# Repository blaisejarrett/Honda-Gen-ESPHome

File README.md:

# Honda-Gen-ESPHome
Honda EU7000is Generator [ESPHome](https://esphome.io/) Integration.

It enables Remote Start and extensive sensor monitoring on the
Fuel Injected Honda EU7000is over wifi.

This project provides two Integrations. They can be used separately or together.

Addionally there is Open Source hardware available for use or for reference
[Here](hardware/README.md)

## Remote Start

Provides a Home Assistant Switch which implements remote start logic.

You must provide 3 GPIO inputs for this to work:
* (Input) Engine running
* (Output) Start Button
* (Output) Engine Kill Switch

In addition, you can optionally provide
* (Input) Power Switch Sensor

If you provide the power switch sensor it will not allow start attempts
if the engine power switch is off.

**Example GPIO configurations**:
```yaml
binary_sensor:
  - platform: gpio
    pin: ${run_pin}
    name: "${upper_devicename} Running Light"
    id: "run_sensor"
  - platform: gpio
    pin: ${sw_pin}
    name: "${upper_devicename} Power Sw Enabled"
    id: "power_sw_sensor"

output:
  - platform: gpio
    pin: ${start_pin}
    id: "start_button"
  - platform: gpio
    pin: ${stop_pin}
    id: "stop_relay"
```

**Example Remote Start Switch Configuration**

```yaml
switch:
  - platform: honda_gen_remote_start
    name: "${upper_devicename} Remote Start"
    # This one's optional. If you provide it then it won't
    # allow start attempts if the power switch is off.
    power_sw_input: power_sw_sensor
    # The following are required.
    run_input: run_sensor
    start_output: start_button
    stop_output: stop_relay
```

For a full example see [Here](example_honda_gen_remote_start.yaml)

## Data Link Connector (DLC) Sensors
The EU7000is is Fuel Injected and features an engine computer.
You can read the ECU's sensor values via a UART bus.

This integration implements a UART device which provides a number of sensors.

Some of the more useful ones:
* Power Output
    * Combined and for each phase
* Engine RPM
* Eco mode on/off
* Engine Throttle
* Engine Run Time
* Temperatures

To use this you must provide a UART interface. There are some hardware considerations.
I recommend you check out the hardware portion of this project [here](hardware/README.md) for reference.

**Implement a UART interface:**
```yaml
uart:
  rx_pin: ${dlc_rx_pin}
  tx_pin: ${dlc_tx_pin}
  baud_rate: 9600
```
**Example Configuration**
```yaml
honda_gen_dlc:
  # if the power is off it won't bother attempting to query sensor values.
  power_switch: power_sw_sensor

  battery_voltage:
    name: "${upper_devicename} Battery Voltage"
  engine_rpm:
    name: "${upper_devicename} Engine RPM"
  runtime:
    name: "${upper_devicename} Total Engine Runtime"
  cylinder_head_temperature:
    name: "${upper_devicename} Cylinder Head Temperature"
  engine_timing:
    name: "${upper_devicename} Engine Spark Timing"
  output_voltage:
    name: "${upper_devicename} Output Voltage"

  barometric_pressure:
    name: "${upper_devicename} Barometric Pressure"
  fuel_injection_time:
    name: "${upper_devicename} Fuel Injection Time"
  throttle:
    name: "${upper_devicename} Trottle Position"
  output_power:
    name: "${upper_devicename} Output Power"
  starter_count:
    name: "${upper_devicename} Starter Count"
  o2_sensor:
    name: "${upper_devicename} O2 Sensor"

  inv_master_current:
    name: "${upper_devicename} Master Inv Current"
  inv_master_temperature:
    name: "${upper_devicename} Master Inv Temperature"
  inv_master_eco:
    name: "${upper_devicename} Eco Mode"
  inv_master_power:
    name: "${upper_devicename} Master Inv Power"
  inv_master_volts:
    name: "${upper_devicename} Master Inv Voltage"

  inv_slave_current:
    name: "${upper_devicename} Slave Inv Current"
  inv_slave_temperature:
    name: "${upper_devicename} Slave Inv Temperature"
  inv_slave_power:
    name: "${upper_devicename} Slave Inv Power"
```

You can optionally provide a power switch sensor. If you do it will not
attempt to query the ECU values over UART if the power switch is off.
Otherwise, it will continually send TX packets and time out if you do not
provide one and the Generator's power switch is off.

You can exclude any sensors from the configuration you do not find 
valuable. The complete list is in the configuration example above.

For a full example see [Here](example_honda_gen_dlc.yaml). Here's an example 
which [includes both integrations](example_honda_gen_complete.yaml).

## Installation with ESPHome

You can use install these integrations just by adding the following to your
esphome project's yaml.
```yaml
external_components:
  - source: github://blaisejarrett/Honda-Gen-ESPHome@main
    components: [ honda_gen_dlc, honda_gen_remote_start ]
```

## Disclaimer
This was tested on a Canadian Model EU7000is. I believe it will work
on US model's aswell. However, 2021+ US models have Bluetooth remote start
features built in. I am told that the remote start port functiality of
this model is different.

Hopefully it works for you. If it does or doesn't I would be interested in
updating this readme.

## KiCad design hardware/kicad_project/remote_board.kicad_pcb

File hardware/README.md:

# Honda Gen Remote Hardware

Here you will find a kicad project and schematic for building an esp32
remote for your honda EU7000is.

The purpose of this device is to interface an esp32 with the DLC port and
the remote start port. This project uses optical isolators between the 
generator and the esp32 microcontroller.

## Schematic
The schematic for this project is available [here](schematic.pdf?raw=true).

It's useful to reference the Honda Gen schematic aswell to understand how to wire
the connectors:

## The Remote Start Connector
The remote start connector uses a [Sumitomo HM 6090-1021 Connector](https://prd.sws.co.jp/components/en/detail.php?number_s=60901021)

It has 8 pins. 5 of which are populated.

| Pin | Description        | Color |
| --- | ------------------ | ----- |
| 1   | Kill SW p2         | Brown/Blue |
| 2   | Running Indicator  | Green/Blue |
| 3   | N/A                |       |
| 4   | N/A                |       |
| 5   | Kill SW p1         | White/Blue |
| 6   | Start              | White/Green |
| 7   | N/A                |       |
| 8   | GND                | Green |

When looking at the female connector on the generator. The pins
are in the following order:
```
8 7 6 5
4 3 2 1
```

## The DLC Connector
The physical connector is described here: https://github.com/blaisejarrett/Honda-Gen-PGM-FI-Protocol#physical-layer

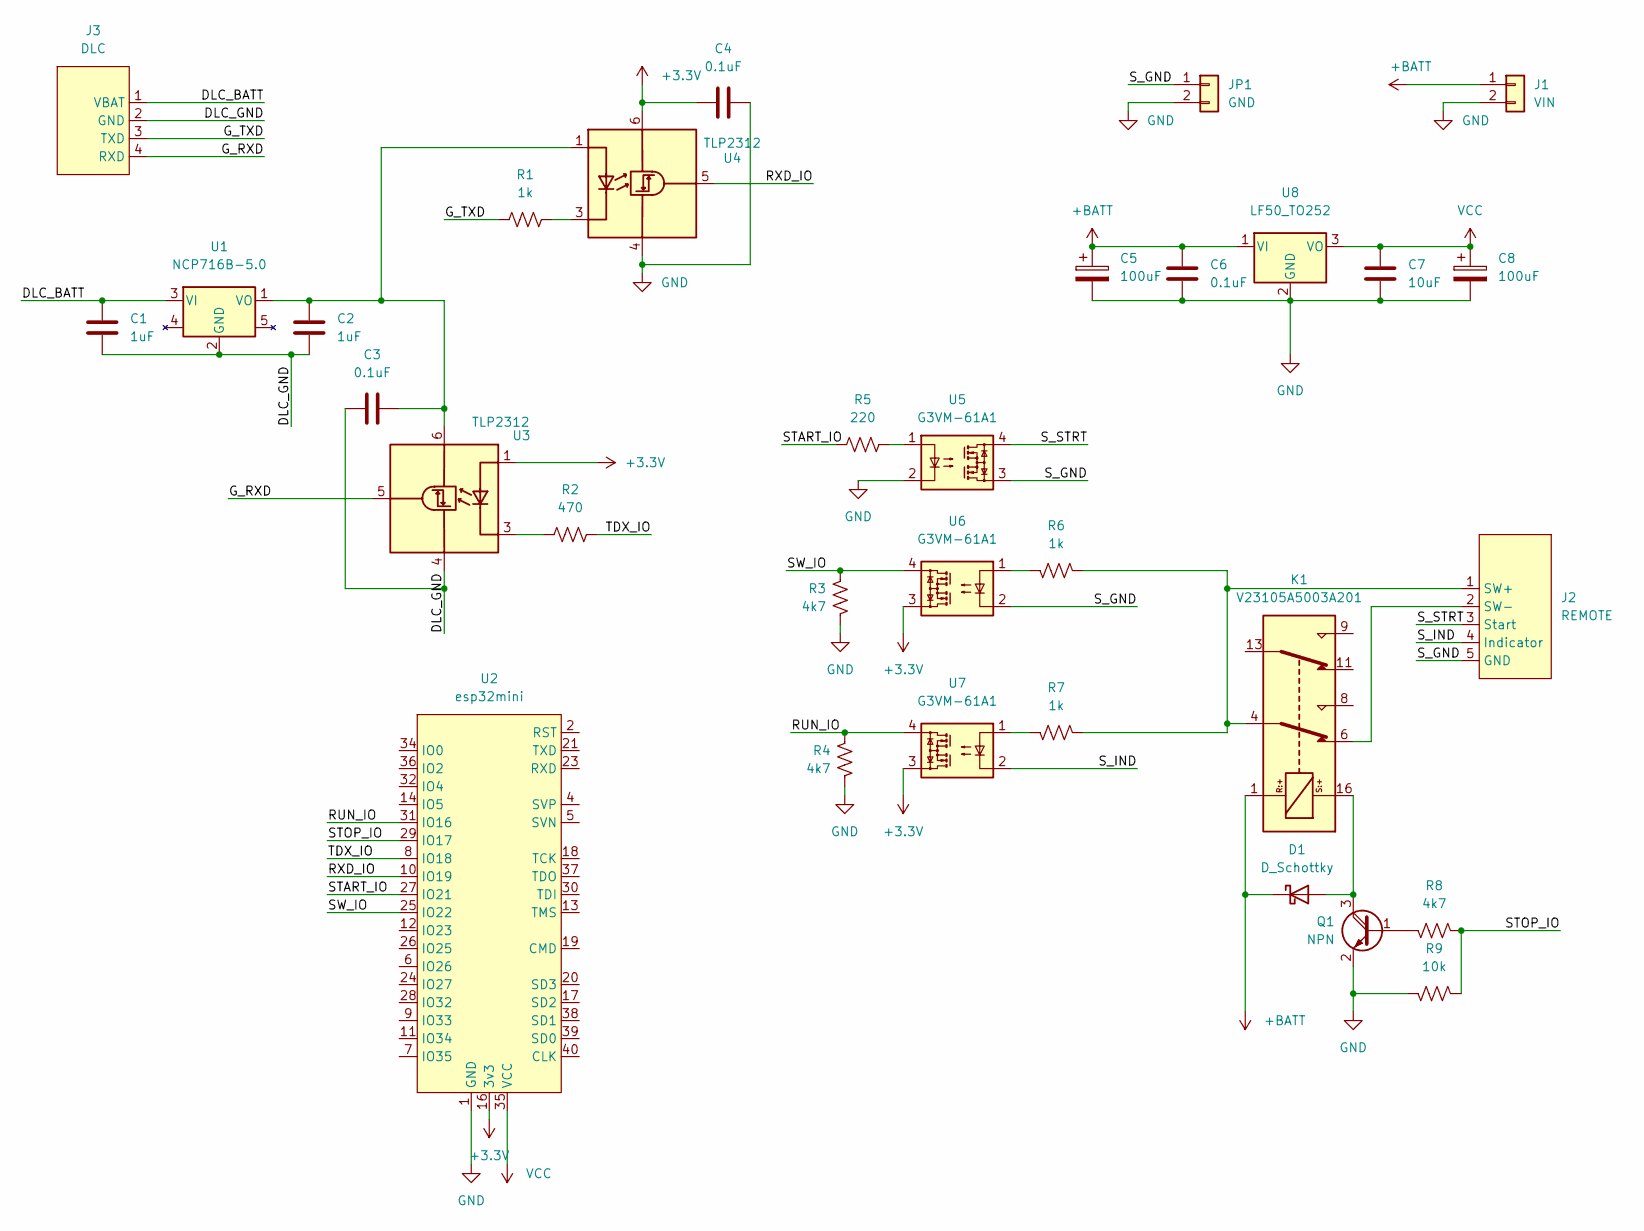
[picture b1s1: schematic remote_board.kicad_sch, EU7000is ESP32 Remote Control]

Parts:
C1, C2: 1uF; C_0805_2012Metric
C3, C4, C6: 0.1uF; C_0805_2012Metric
C5, C8: 100uF; CP_Elec_6.3x5.8
C7: 10uF; C_1206_3216Metric
D1: D_Schottky; D_0805_2012Metric
J1: VIN; PinHeader_1x02_P2.54mm_Vertical
J2: REMOTE; PinHeader_1x05_P2.54mm_Vertical
J3: DLC; PinHeader_1x04_P2.54mm_Vertical
JP1: GND; PinHeader_1x02_P2.54mm_Vertical
K1: V23105A5003A201
Q1: NPN; SOT-23
R1, R6, R7: 1k; R_0805_2012Metric
R2: 470; R_0805_2012Metric
R3, R4, R8: 4k7; R_0805_2012Metric
R5: 220; R_0805_2012Metric
R9: 10k; R_0805_2012Metric
U1: NCP716B-5.0; TSOP-5_1.65x3.05mm_P0.95mm
U2: esp32mini; ESP32_mini
U3, U4: TLP2312; SO-5_4.4x3.6mm_P1.27mm
U5, U6, U7: G3VM-61A1; DIP-4_W7.62mm
U8: LF50_TO252; TO-252-2

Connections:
+3V3: C4.1, U2.16 (3v3), U3.1 (A), U4.6 (VDD), U6.3, U7.3
+BATT: C5.1, C6.1, D1.1 (K), J1.1, K1.1, U8.1 (VI)
/DLC_BATT: C1.1, J3.1 (VBAT), U1.3 (VI)
/DLC_GND: C1.2, C2.2, C3.2, J3.2 (GND), U1.2 (GND), U3.4 (GND)
/G_RXD: J3.4 (RXD), U3.5 (VO)
/G_TXD: J3.3 (TXD), R1.1
/RUN_IO: R4.2, U2.31 (IO16), U7.4
/RXD_IO: U2.10 (IO19), U4.5 (VO)
/START_IO: R5.1, U2.27 (IO21)
/STOP_IO: R8.1, R9.1, U2.29 (IO17)
/SW_IO: R3.2, U2.25 (IO22), U6.4
/S_GND: J2.5 (GND), JP1.1, U5.3, U6.2
/S_IND: J2.4 (Indicator), U7.2
/S_STRT: J2.3 (Start), U5.4
/TDX_IO: R2.2, U2.8 (IO18)
GND: C4.2, C5.2, C6.2, C7.2, C8.2, J1.2, JP1.2, Q1.2 (E), R3.1, R4.1, R9.2, U2.1 (GND), U4.4 (GND), U5.2, U8.2 (GND)
unnamed: C2.1, C3.1, U1.1 (VO), U3.6 (VDD), U4.1 (A)
unnamed: D1.2 (A), K1.16, Q1.3 (C)
unnamed: J2.1 (SW+), K1.4, R6.1, R7.1
unnamed: J2.2 (SW-), K1.6
unnamed: Q1.1 (B), R8.2
unnamed: R2.1, U3.3 (K)
unnamed: R5.2, U5.1
unnamed: R6.2, U6.1
unnamed: R7.2, U7.1
unnamed: R1.2, U4.3 (K)
VCC: C7.1, C8.1, U2.35 (VCC), U8.3 (VO)

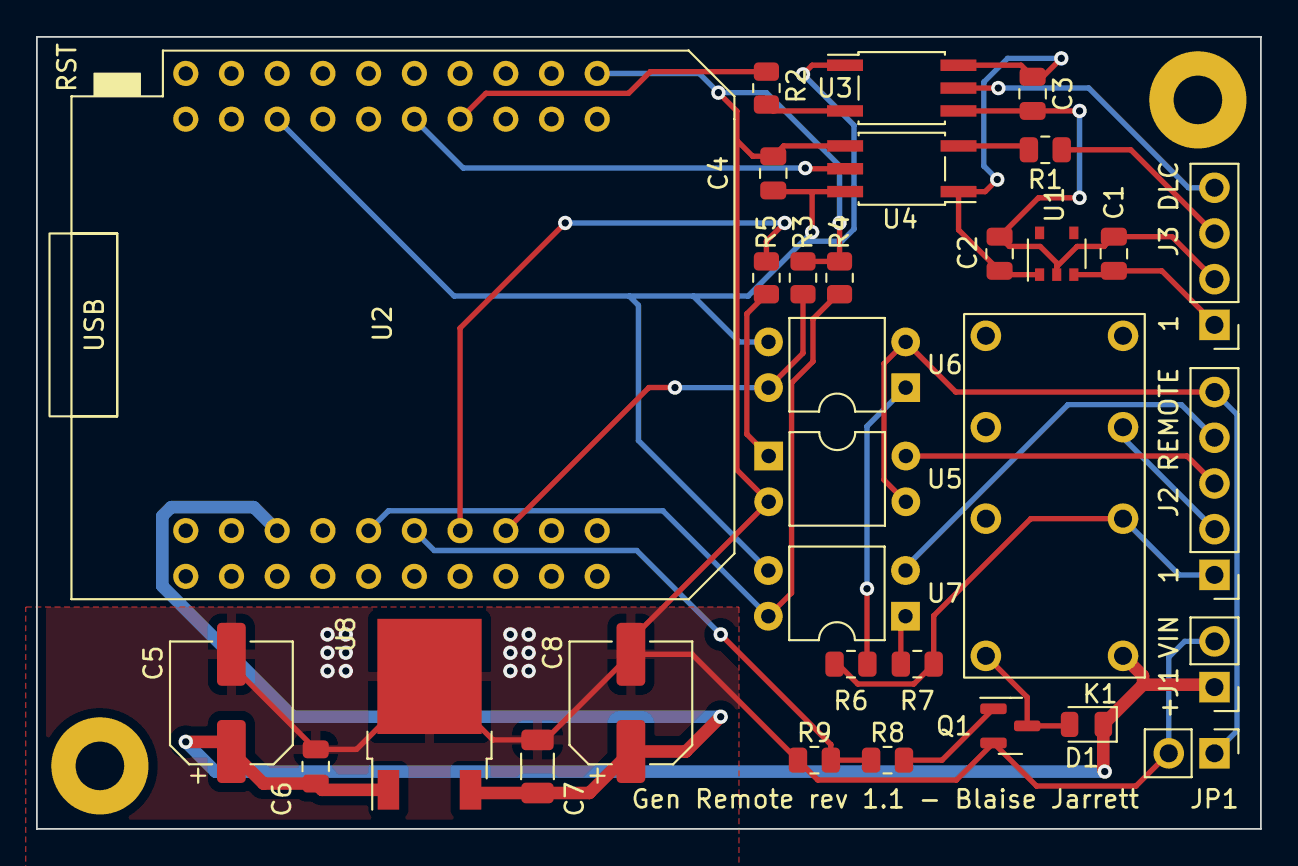
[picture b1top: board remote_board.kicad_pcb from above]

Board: 2 copper layers, 68.0 x 44.0 mm, 32 parts (0 on the bottom side), 27 nets.

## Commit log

2022-01-25 work in progress. Reads DLC sensors from ECU info1 and ECU info2
2022-01-25 Added Inverter Master Query.
2022-01-26 Added Inverter Slave Query.
2022-01-26 Remote Start Switch template. It compiles. Not yet implemented.
2022-01-26 Remote Start implementation. Fix for DLC. must include hal for millis()
2022-01-26 Remote start fix. It appears to work!
2022-01-26 Example esphome yaml for remote start. Updated DLC example to add additional sensors.
2022-01-26 Readme doc. Complete example for esphome configuration.
2022-01-26 Fixing doc screenies
2022-01-26 Missing doc images
2022-01-26 Incorrect external_components for full example
2022-01-26 More doc improvements
2022-01-27 Added the hardware project.
2022-01-27 Main docs now include a reference to the hardware project. Added PCB screenshot.
